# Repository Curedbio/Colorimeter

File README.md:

# Colorimeter

Educational open-source colorimeter

- Arduino UNO based.
- Sensor TCS3200.
- RGB PCB board mounts RGB LED (Red 632 nm; Green 523 nm; 465 nm) 
- Single LED PCB board.

*Derived from IO Rodeo's OSHW Colorimeter*

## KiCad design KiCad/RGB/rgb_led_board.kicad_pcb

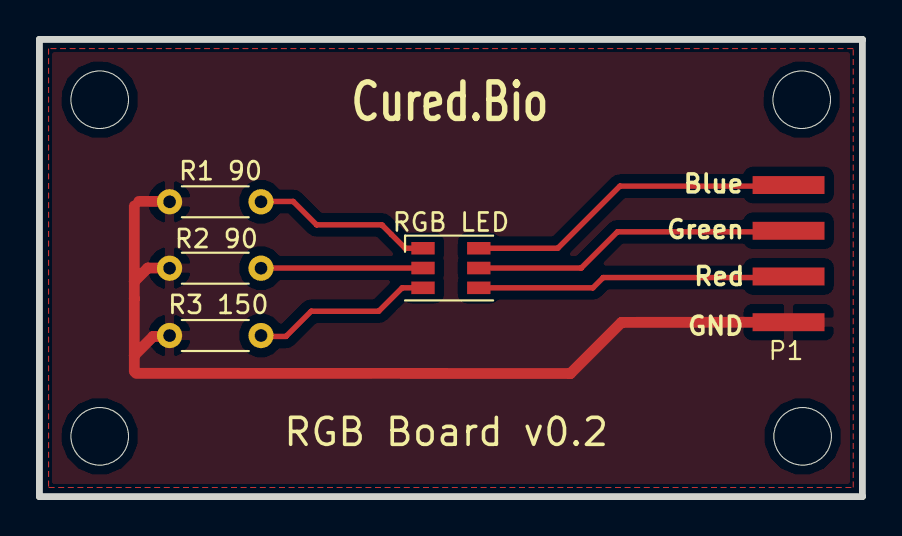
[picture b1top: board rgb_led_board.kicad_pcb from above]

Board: 2 copper layers, 45.7 x 25.4 mm, 9 parts (0 on the bottom side), 7 nets.

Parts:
1, 2, 3, 4: MountingHole_3.2mm_M3_ISO14580
P1: P1; 1X04_SMD_LONG
R1 90, R2 90: 90; R_Axial_DIN0204_L3.6mm_D1.6mm_P5.08mm_Horizontal
R3 150: 150; R_Axial_DIN0204_L3.6mm_D1.6mm_P5.08mm_Horizontal
RGB LED: RGB_LED; LED_RGB_PLCC-6

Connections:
/blue: P1.1, RGB LED.A1
/green: P1.2, RGB LED.A2
/red: P1.3, RGB LED.A3
GND: P1.4, R1 90.2, R2 90.2, R3 150.2
unnamed: R1 90.1, RGB LED.C1
unnamed: R2 90.1, RGB LED.C2
unnamed: R3 150.1, RGB LED.C3

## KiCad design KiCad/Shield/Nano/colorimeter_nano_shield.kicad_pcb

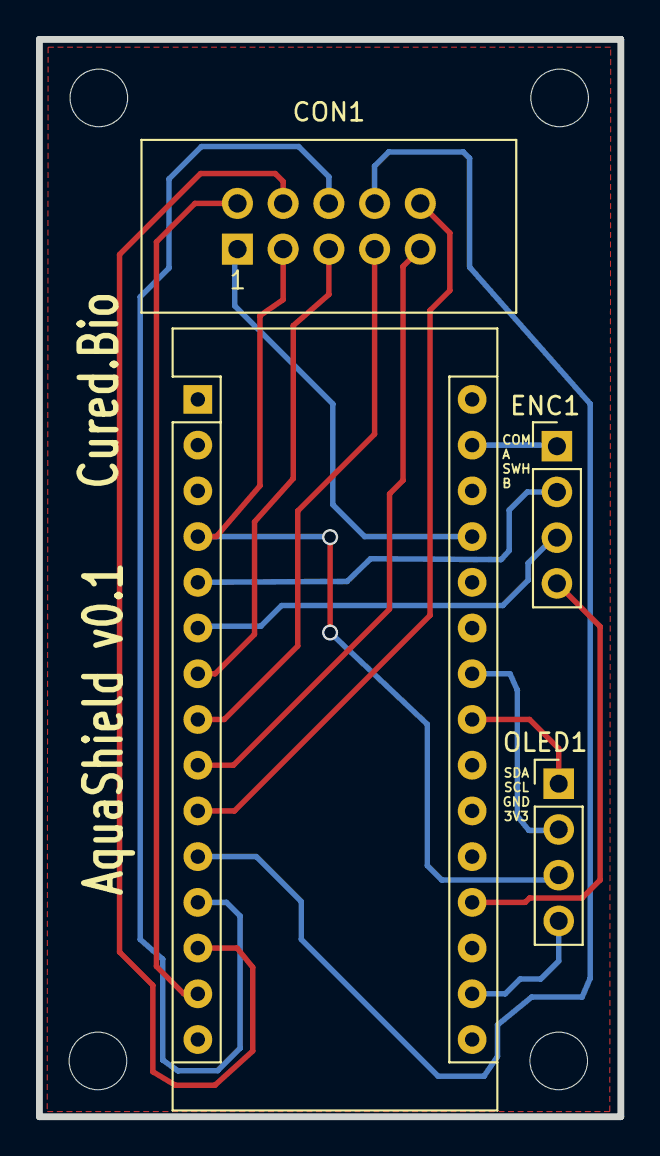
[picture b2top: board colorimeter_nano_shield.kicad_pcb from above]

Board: 2 copper layers, 32.3 x 59.9 mm, 8 parts (0 on the bottom side), 17 nets.

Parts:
1, 2, 3, 4: MountingHole_3.2mm_M3_ISO14580
CON1: CONN_5X2; IDC-Header_2x05_Pitch2.54mm_Straight
ENC1: CONN_01X04_MALE; Pin_Header_Straight_1x04_Pitch2.54mm
OLED1: CONN_01X04_MALE; Pin_Header_Straight_1x04_Pitch2.54mm
U1: ARDUINO_NANO; Arduino_Nano

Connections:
3V3: OLED1.4, U1.17
5V: CON1.1, U1.27
A: ENC1.2, U1.5
B: ENC1.4, U1.19
BLUE: CON1.6, U1.12
COM: ENC1.1, U1.29
FREQ: CON1.8, U1.11
GND: CON1.3, OLED1.3, U1.4
GREEN: CON1.4, U1.13
RED: CON1.2, U1.14
S0: CON1.5, U1.7
S1: CON1.7, U1.8
S2: CON1.9, U1.9
S3: CON1.10, U1.10
SCL: OLED1.2, U1.24
SDA: OLED1.1, U1.23
SWITCH: ENC1.3, U1.6

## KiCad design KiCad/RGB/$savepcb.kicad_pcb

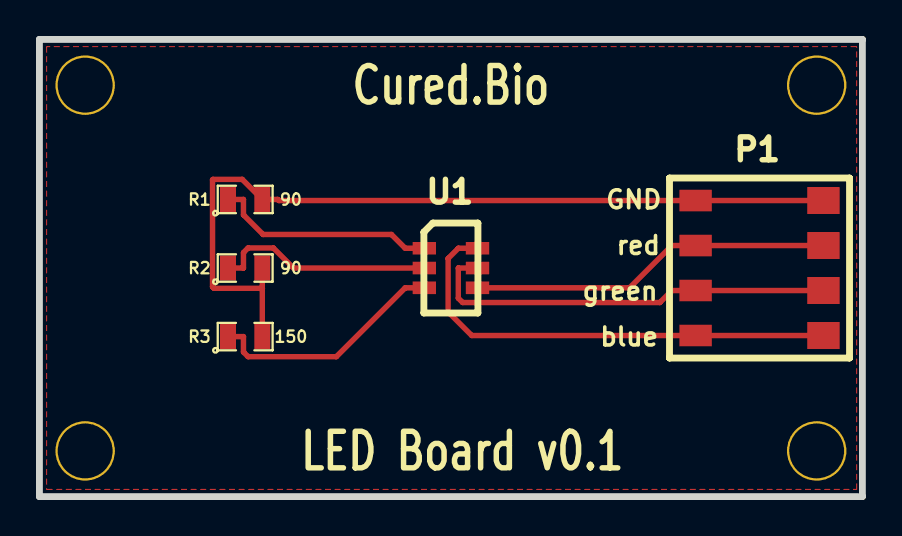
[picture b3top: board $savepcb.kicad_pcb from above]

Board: 2 copper layers, 45.7 x 25.4 mm, 9 parts (0 on the bottom side), 7 nets.

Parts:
M1, M2, M3, M4: MOUNT_HOLE_4_40
P1: SMD_wire_4x1
R1, R2: 90; SM0805
R3: 150; SM0805
U1: RGB_MULTILED

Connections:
/blue: P1.1, U1.A1
/green: P1.2, U1.A2
/red: P1.3, U1.A3
GND: P1.4, R1.2, R2.2, R3.2
unnamed: R2.1, U1.C2
unnamed: R3.1, U1.C3
unnamed: R1.1, U1.C1

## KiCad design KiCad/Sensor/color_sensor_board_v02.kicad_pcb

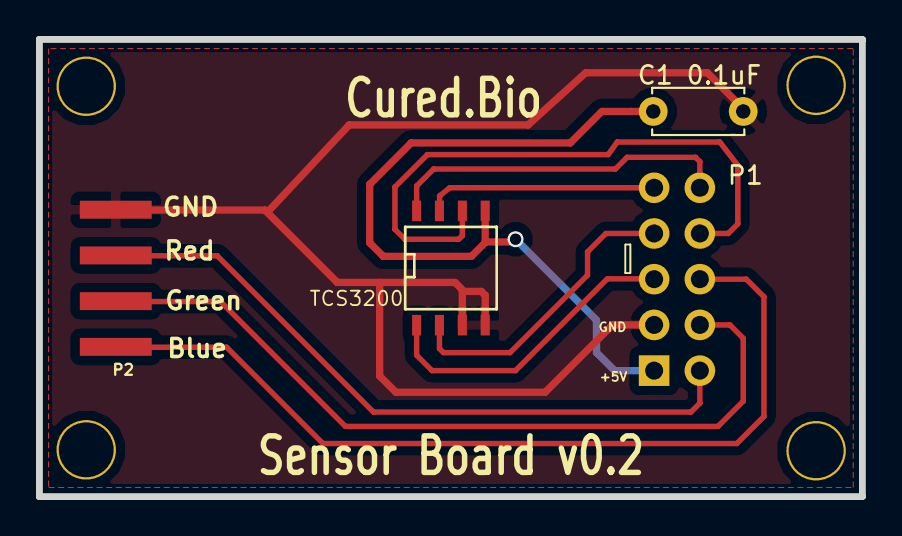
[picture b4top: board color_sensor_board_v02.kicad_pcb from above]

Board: 2 copper layers, 45.7 x 25.4 mm, 8 parts (1 on the bottom side), 10 nets.

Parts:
C1 0.1uF: 0.1 uF; C_Disc_D5.0mm_W2.5mm_P5.00mm
MOUNT_HOLE_1: 1; MOUNT_HOLE_4_40
MOUNT_HOLE_2: 2; MOUNT_HOLE_4_40
MOUNT_HOLE_3: 3; MOUNT_HOLE_4_40
MOUNT_HOLE_4: 4; MOUNT_HOLE_4_40
P1: CONN_5X2; Pin_Header_Straight_2x05_Pitch2.54mm
P2: CONN_4; 1X04_SMD_LONG
TCS3200: TCS3200; SOIC-8-N

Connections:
/5V: C1 0.1uF.1, P1.1, TCS3200.5
/FREQ: P1.8, TCS3200.6
/S0: P1.5, TCS3200.1
/S1: P1.7, TCS3200.2
/S2: P1.9, TCS3200.7
/S3: P1.10, TCS3200.8
/blue: P1.6, P2.1
/green: P1.4, P2.2
/red: P1.2, P2.3
GND: C1 0.1uF.2, P1.3, P2.4, TCS3200.3, TCS3200.4

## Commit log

2018-03-30 Kicad files
2018-03-30 wiindows ver
2018-03-30 Software
2018-04-14 photo
